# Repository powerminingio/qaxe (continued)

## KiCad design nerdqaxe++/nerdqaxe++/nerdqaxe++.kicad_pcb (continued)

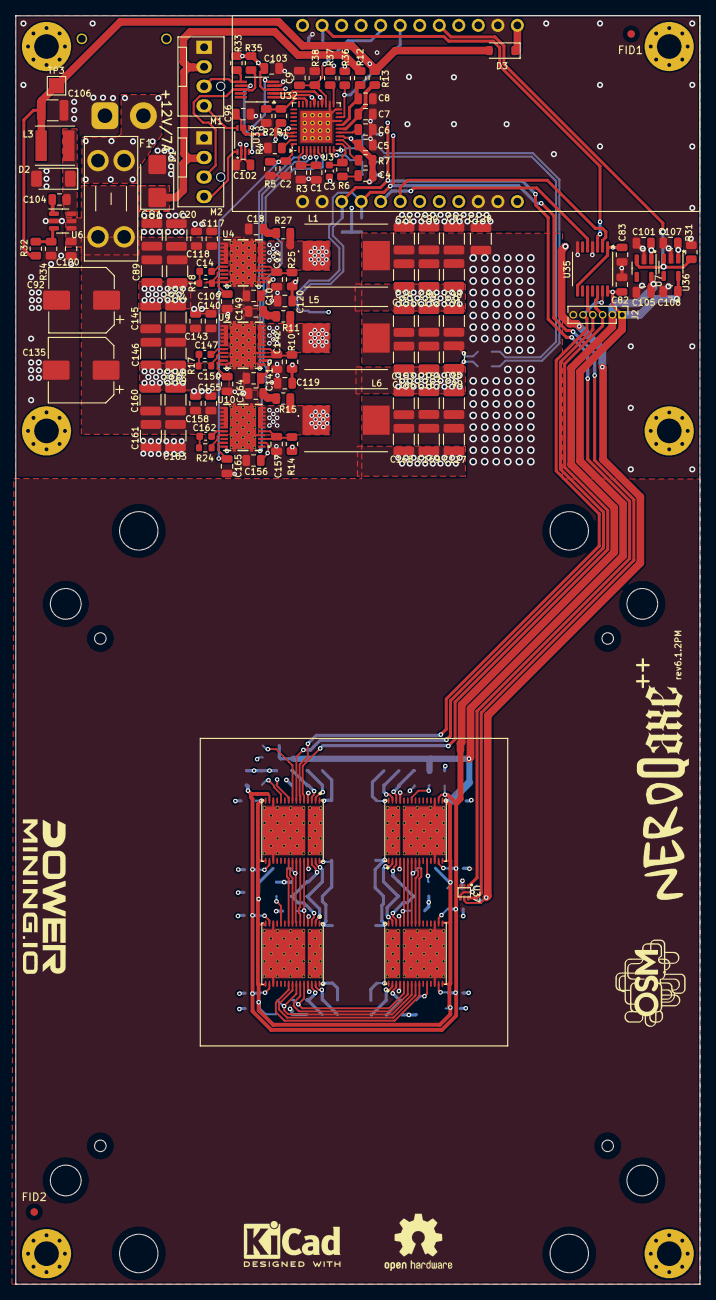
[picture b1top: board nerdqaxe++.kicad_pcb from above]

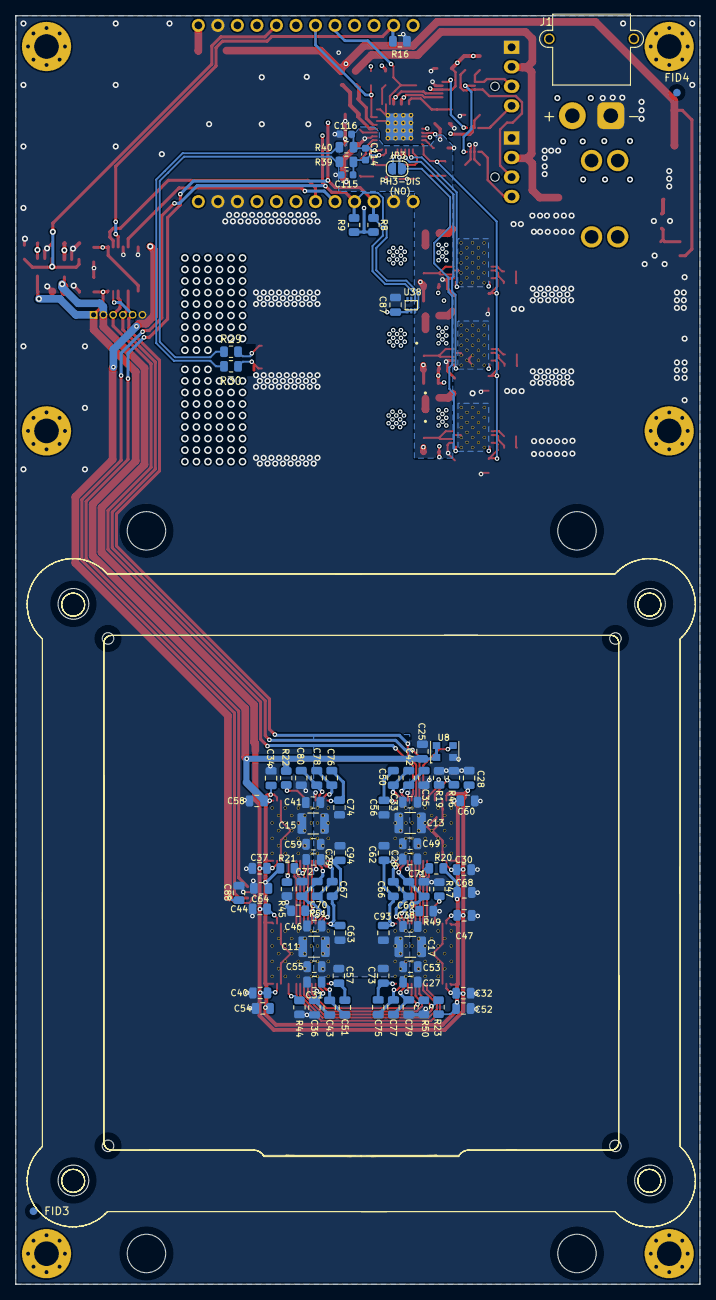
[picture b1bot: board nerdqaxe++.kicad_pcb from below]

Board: 6 copper layers, 89.0 x 165.0 mm, 220 parts (87 on the bottom side), 109 nets.

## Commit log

2025-12-03 Powermining revision
2026-01-26 Edit on rev 6.1PM
    - Moved XT30 connector to the back of the board
    - Edited VDD polygon
    - Fixed various via placements
    - Fixed various tracing
    - Updated BM1370 footprint and solder paste stencil
    - Updated CSD95472Q5MC footprint and solder paste stencil
2026-01-26 Empty branch for shufps qaxe main import
2026-01-26 Import shufps/qaxe into this branch
2026-01-26 Updated PCB layout
    - Replaced barrel jack socket with XT30M
    - Replaced old fuse holder with new 3568
    - Reordered components for AP3211 5V buck converter
2026-01-29 Nerdqaxe++ rev6.1.2PM
    1. BM1370 Footprint solder paste revision
    2. Added 2R2 resistor in series with bootstrap cap for CSD95472Q5MC
    3. 180nH inductors for CSD
    4. Vsense closer to ASICs
    5. Fiducials
    6. Updated top silkscreen
2026-01-30 Nerdqaxe++ rev6.1.2PM
    - Vsense resistors back to their original place
